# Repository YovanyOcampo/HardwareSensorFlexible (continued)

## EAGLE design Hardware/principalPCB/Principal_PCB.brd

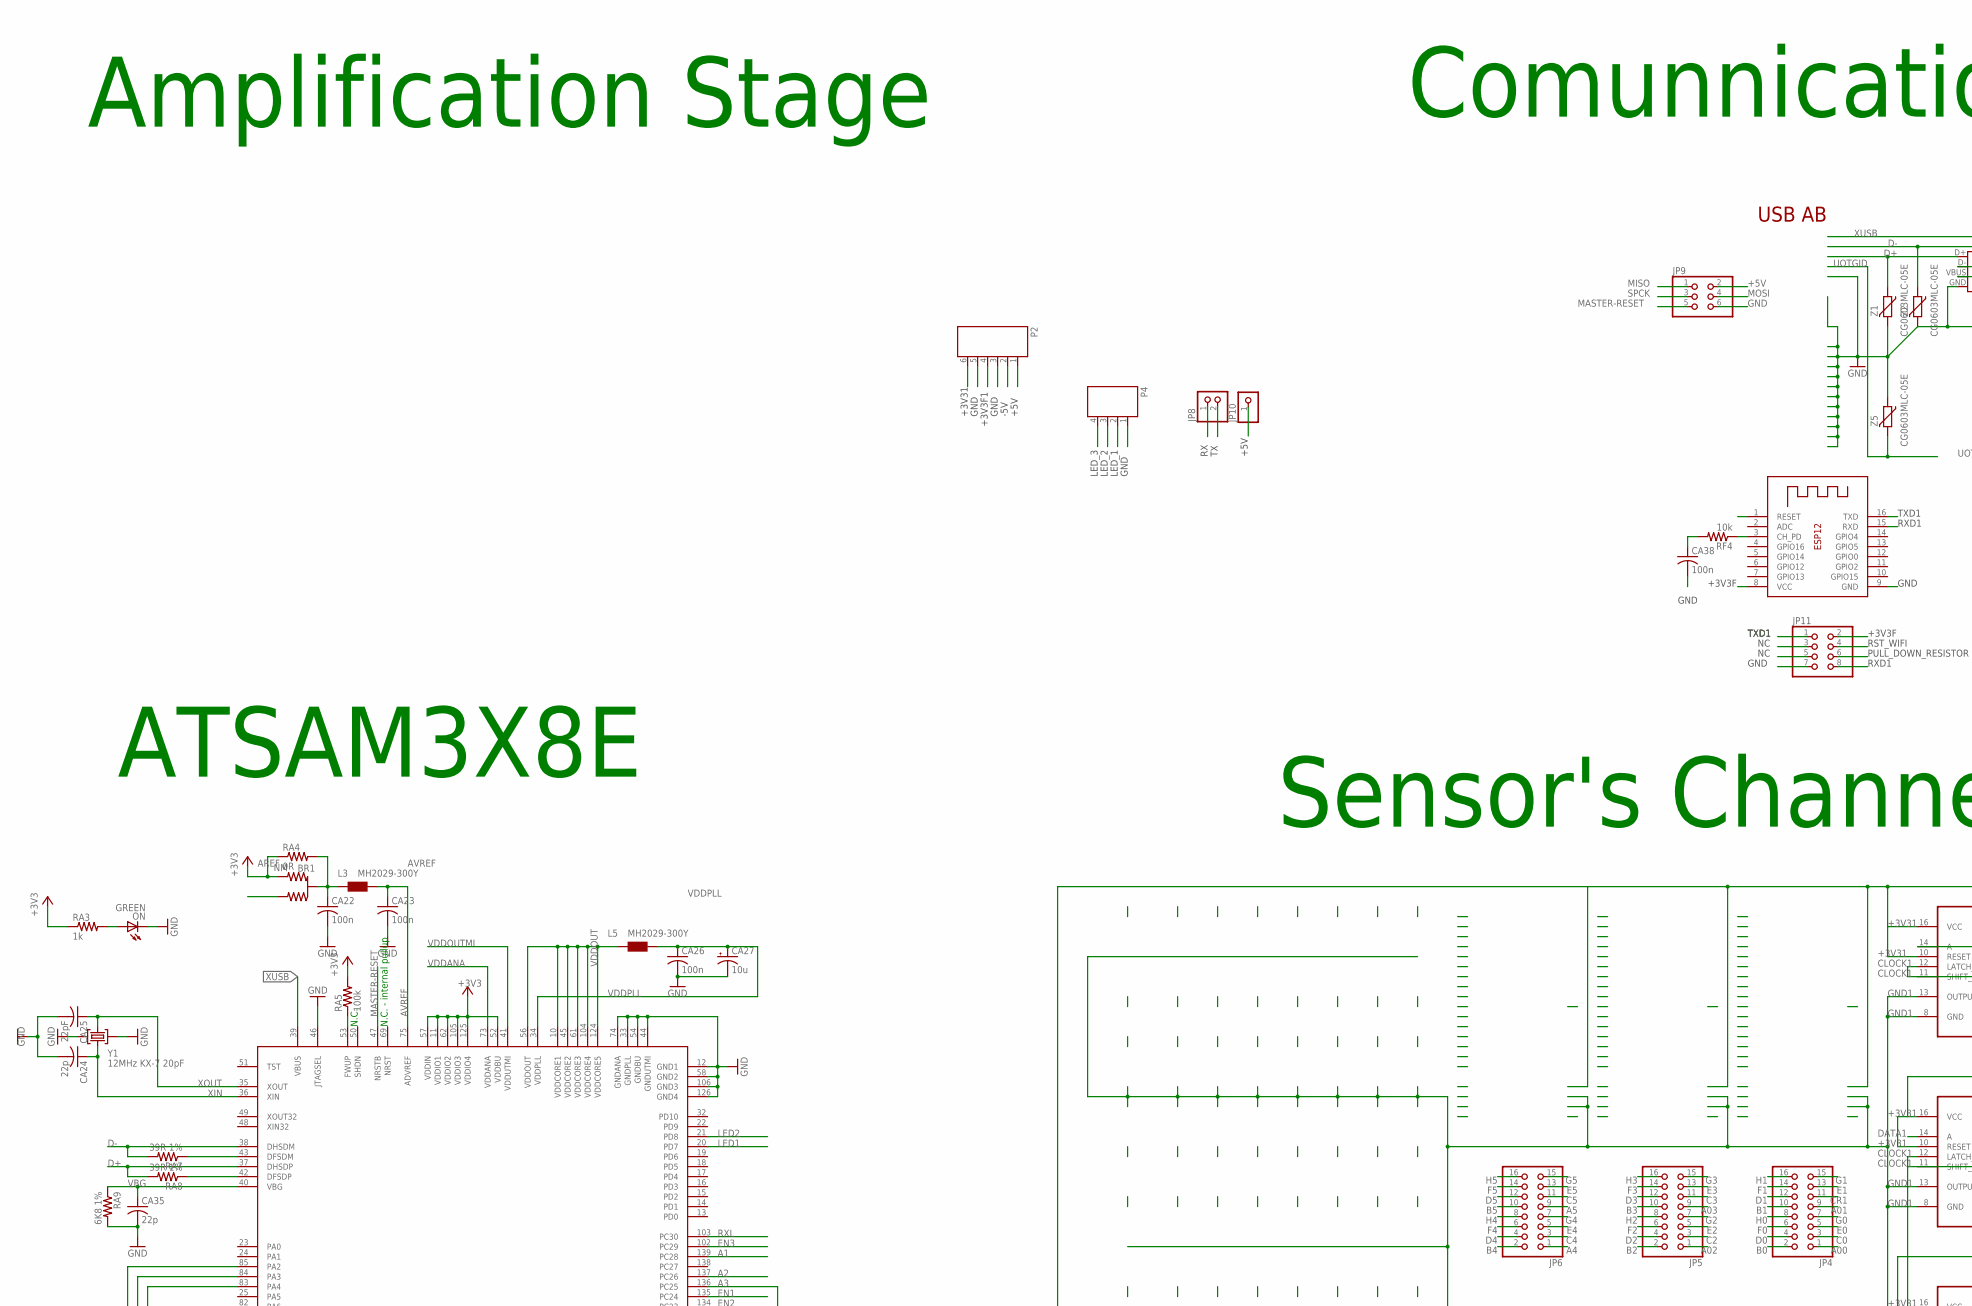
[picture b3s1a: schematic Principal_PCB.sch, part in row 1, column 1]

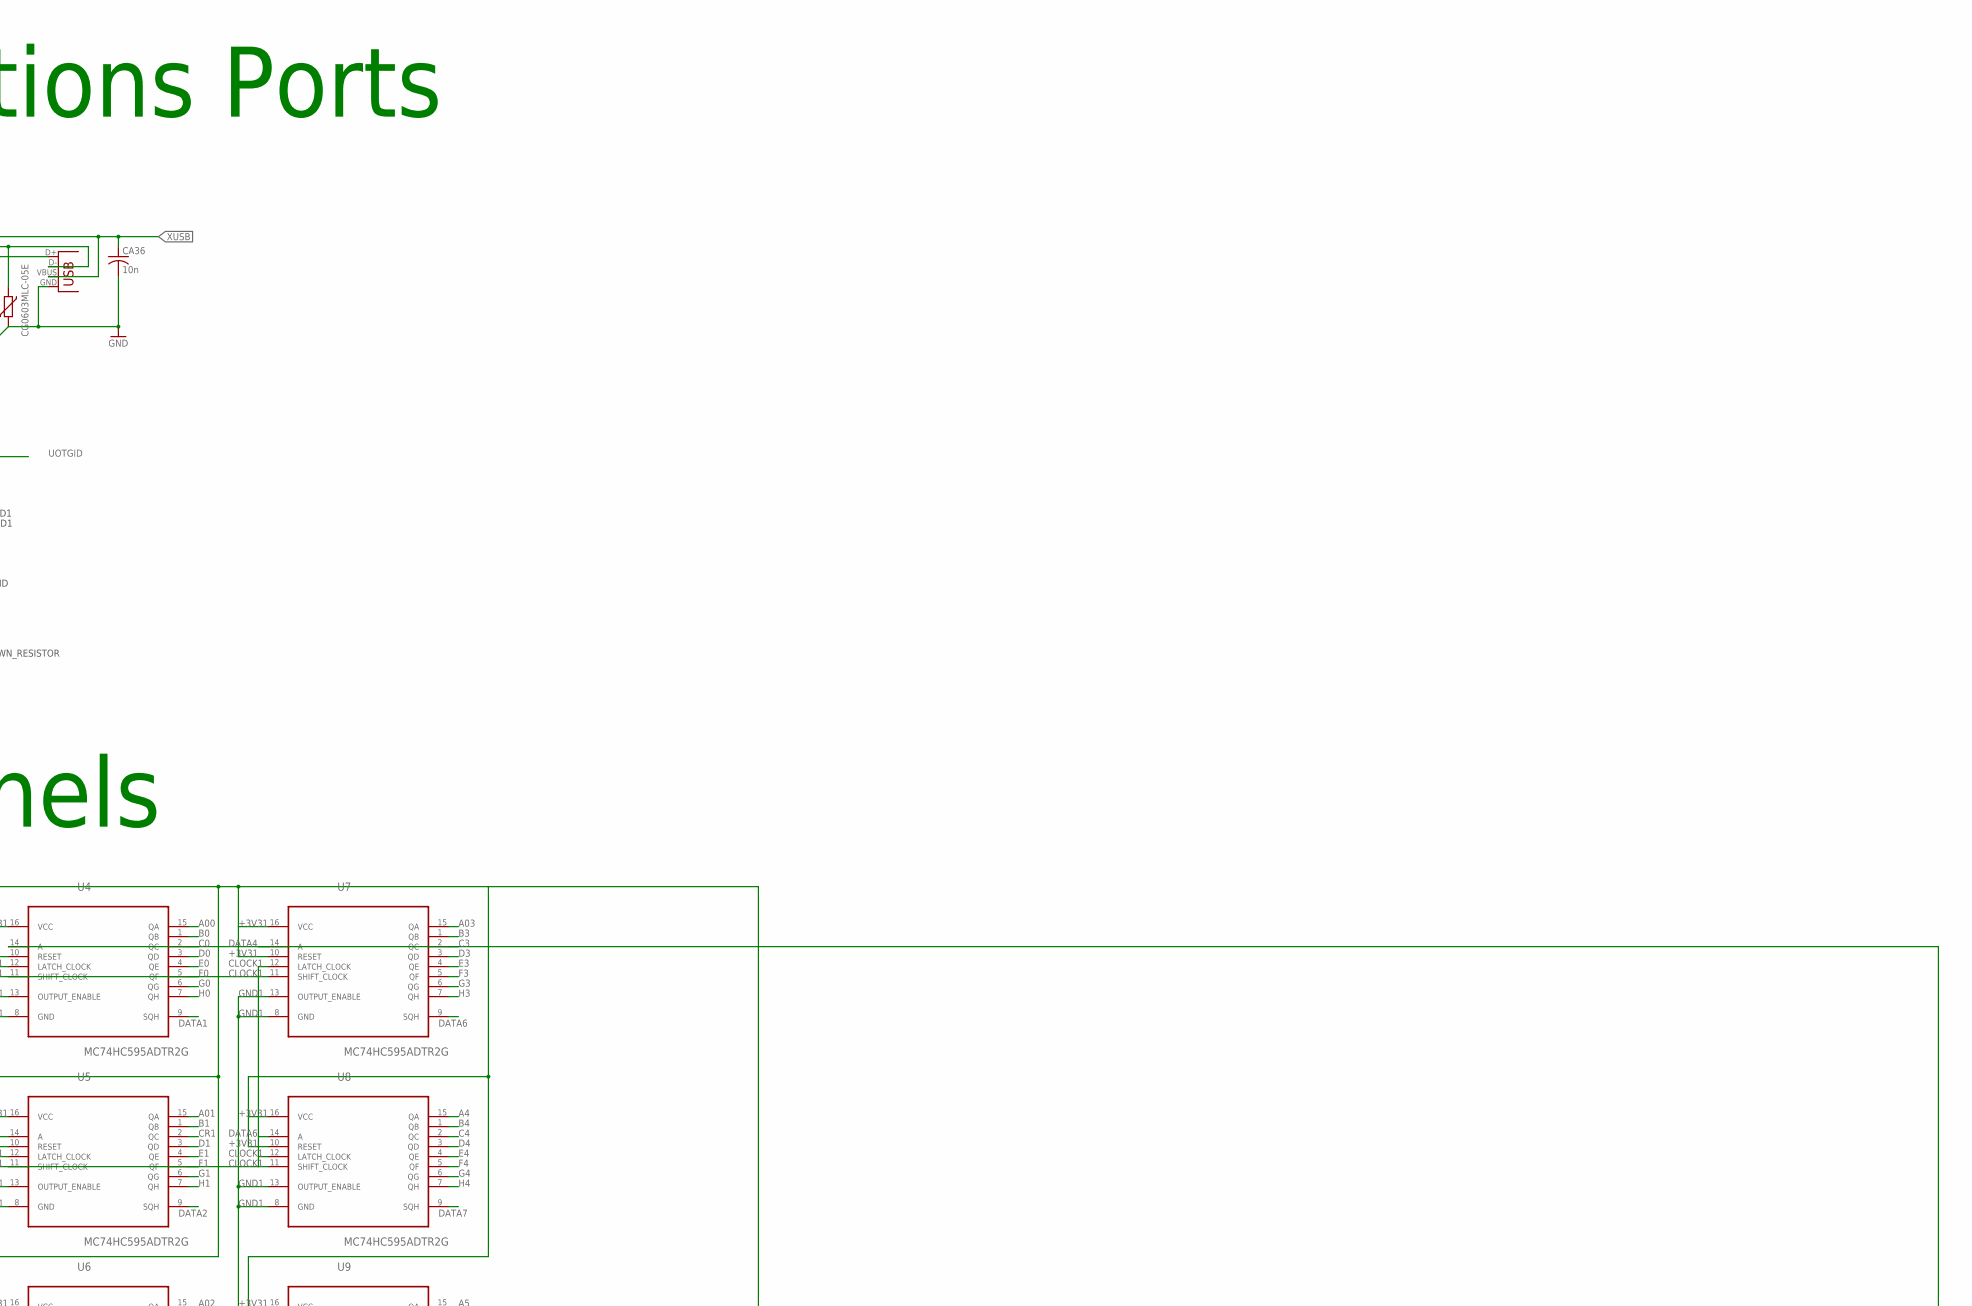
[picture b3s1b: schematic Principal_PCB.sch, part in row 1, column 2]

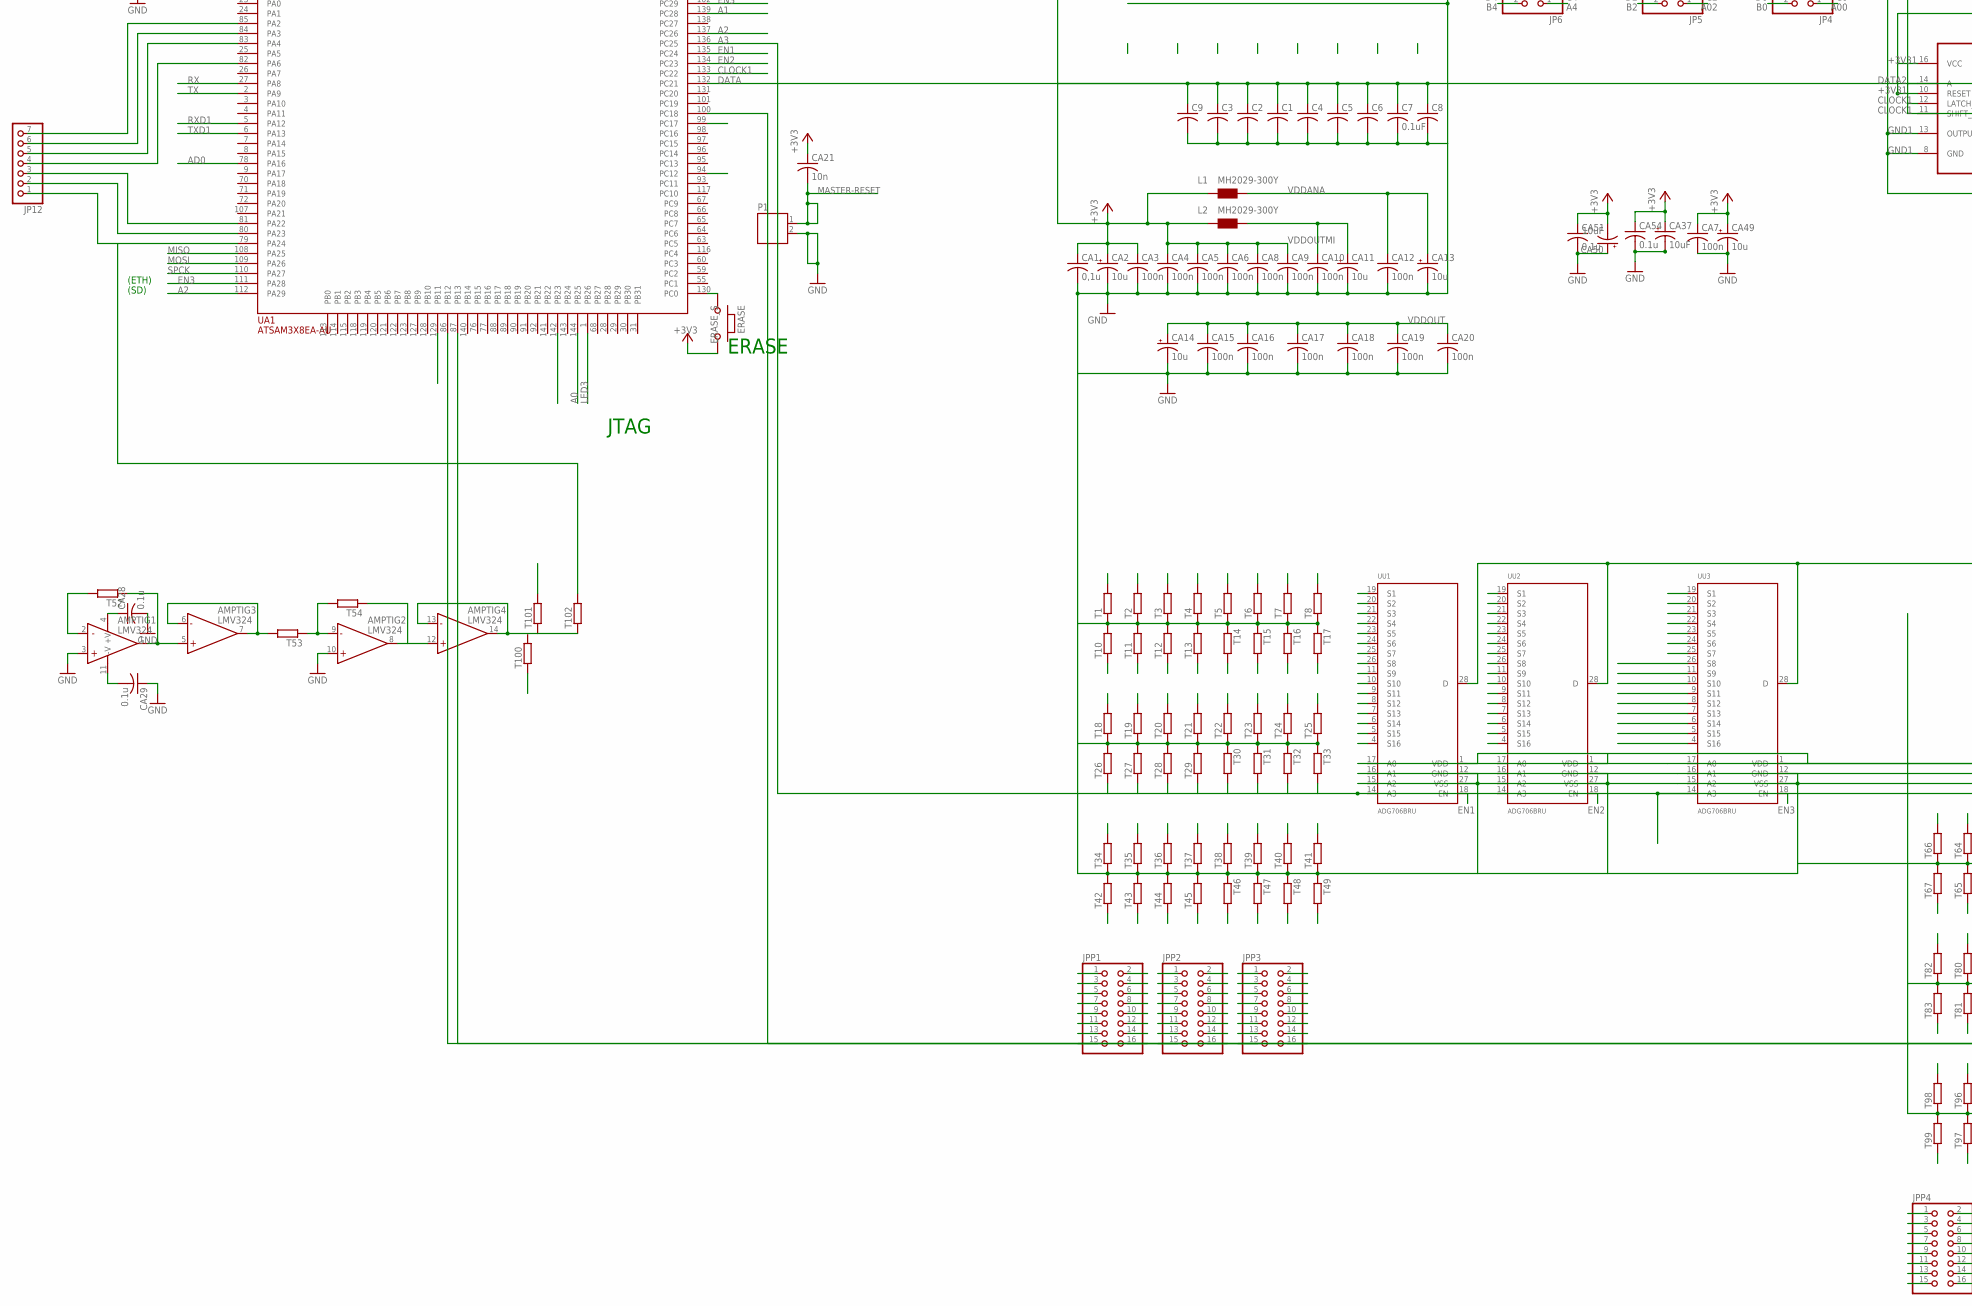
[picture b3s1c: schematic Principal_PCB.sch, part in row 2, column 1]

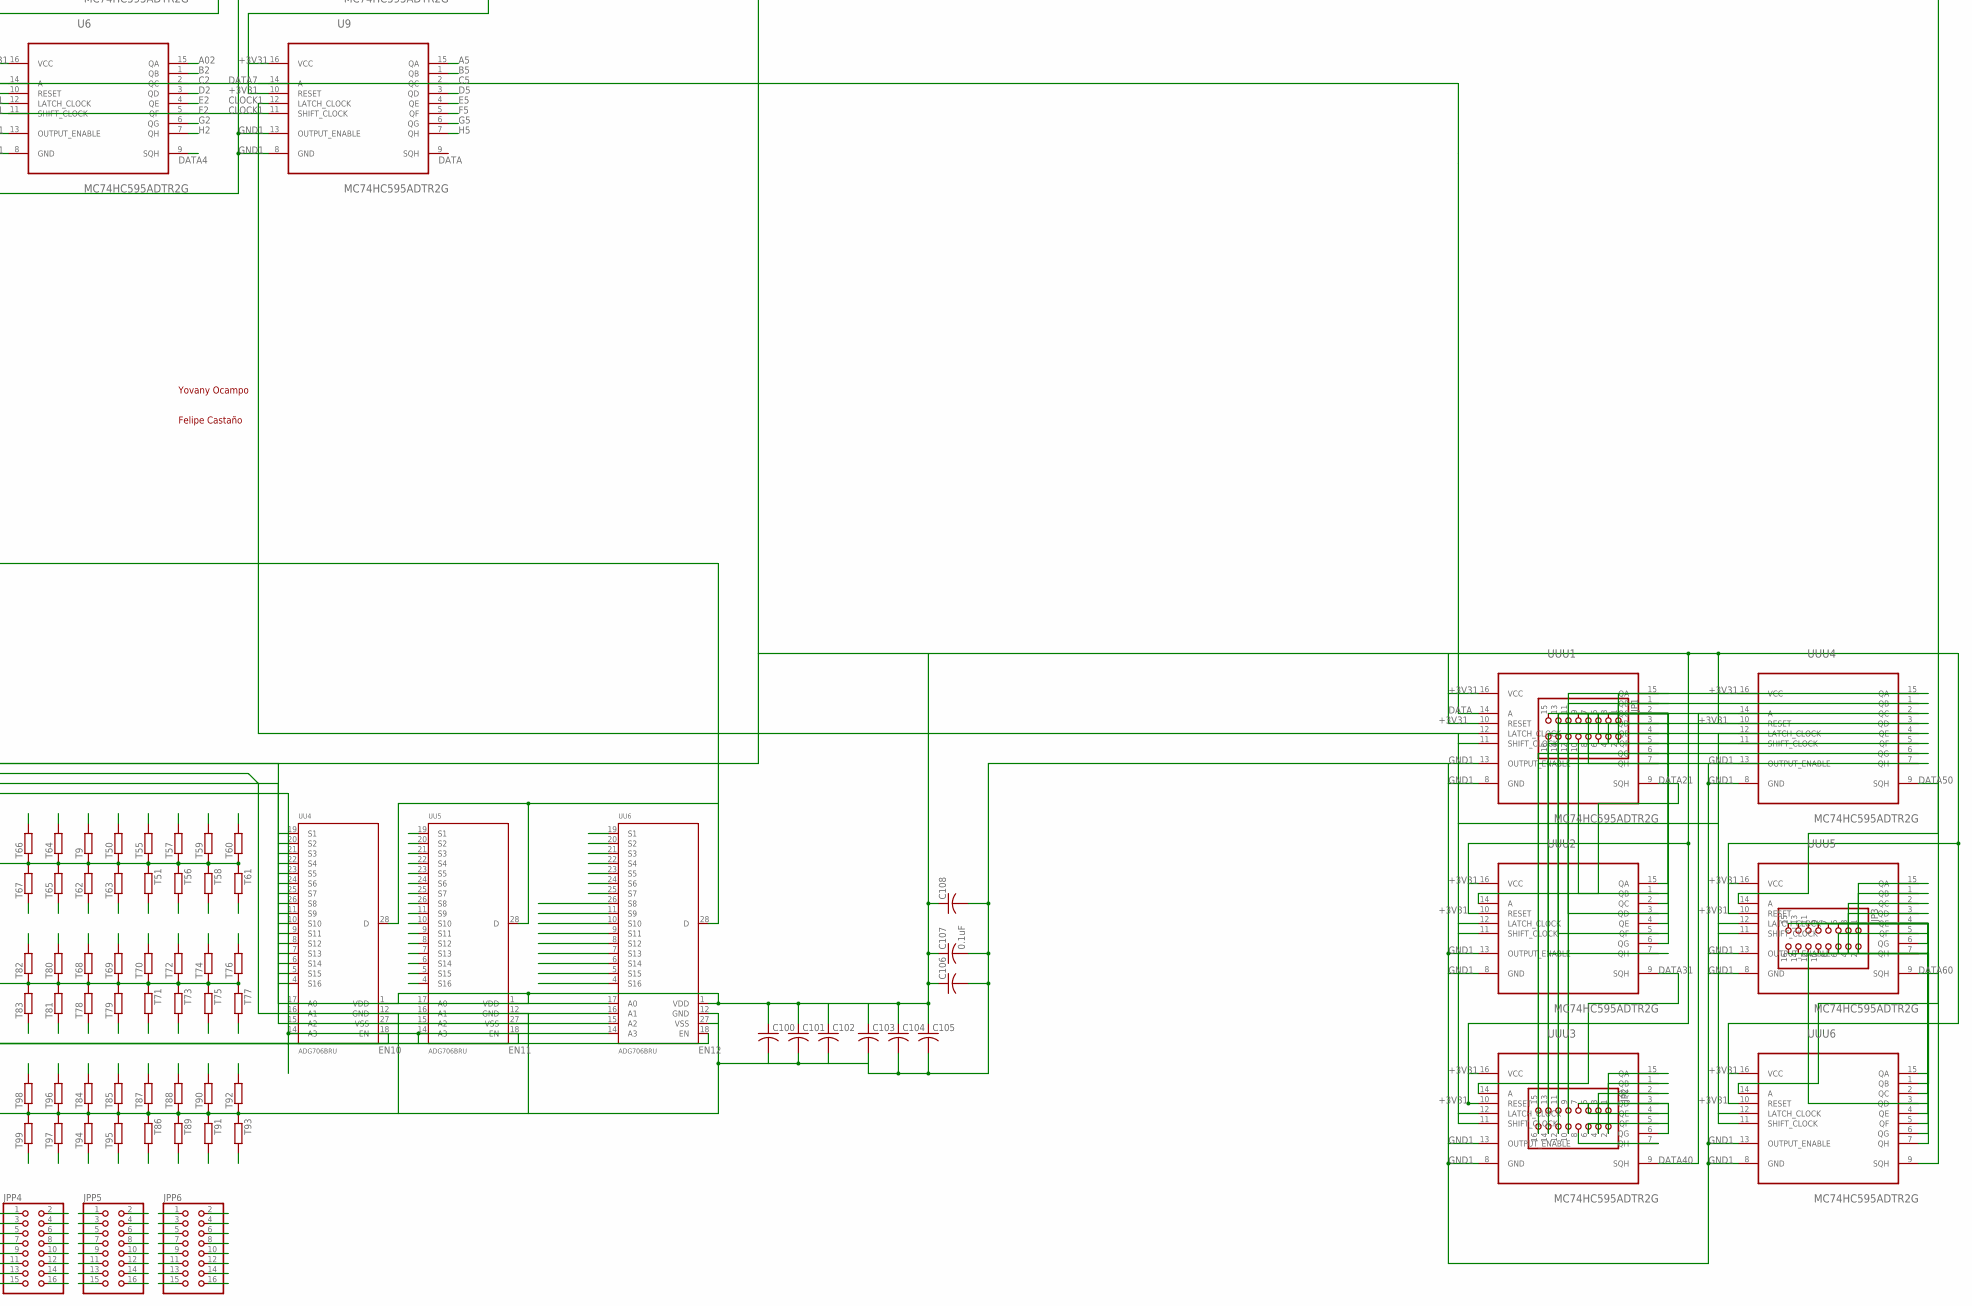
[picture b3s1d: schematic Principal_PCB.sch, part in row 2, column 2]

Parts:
AMPTI: LMV324; SO014
BR1: NM; J0402
C1, C2, C3, C4, C5, C6, C8, C9, C100, C101, C102, C103, C104, C105, C106, C108: C-USC0805; C0805
C7, C107: 0.1uF; C0805
CA1: 0,1u; C0805
CA2, CA11, CA13, CA14, CA27, CA49: 10u; B/3528-21W
CA3, CA4, CA5, CA6, CA7, CA8, CA9, CA10, CA12, CA15, CA16, CA17, CA18, CA19, CA20, CA22, CA23, CA26, CA38: 100n; C0805
CA21, CA36: 10n; C0805
CA24, CA35: 22p; C0805
CA25: 22pF; C0805
CA28, CA29, CA51, CA54: 0.1u; C0805K
CA37, CA50: 10uF; B/3528-21W
ERASE: MYSMD_PB157; SMD_157SW
JP1, JP2, JP3, JP4, JP5, JP6: PINHD-2X8; 2X08
JP8: PINHD-1X2; 1X02
JP9: PINHD-2X3; 2X03
JP10: PINHD-1X1; 1X01
JP11: PINHD-2X4; 2X04
JP12: PINHD-1X7; 1X07
JPP1, JPP2, JPP3, JPP4, JPP5, JPP6: PINHD-2X8; 2X08
L1, L2, L3, L5: MH2029-300Y; 0805
ON: GREEN; CHIP-LED0805
P1: JST-PH2
P2: JST-PH6
P4: JST-PH4
RA3: 1k; R0805
RA4: 0R; R0805
RA5: 100k; R0805
RA7, RA8: 39R 1%; R0805
RA9: 6K8 1%; R0805
RF4: 10k; R0805
T1, T2, T3, T4, T5, T6, T7, T8, T9, T10, T11, T12, T13, T14, T15, T16, T17, T18, T19, T20, T21, T22, T23, T24, T25, T26, T27, T28, T29, T30, T31, T32, T33, T34, T35, T36, T37, T38, T39, T40, T41, T42, T43, T44, T45, T46, T47, T48, T49, T50, T51, T52, T53, T54, T55, T56, T57, T58, T59, T60, T61, T62, T63, T64, T65, T66, T67, T68, T69, T70, T71, T72, T73, T74, T75, T76, T77, T78, T79, T80, T81, T82, T83, T84, T85, T86, T87, T88, T89, T90, T91, T92, T93, T94, T95, T96, T97, T98, T99, T100, T101, T102: R-EU_R0805; R0805
U4, U5, U6, U7, U8, U9: MC74HC595ADTR2G; SOP65P640X120-16N
UA1: ATSAM3X8EA-AU; LQFP144
UU1, UU2, UU3, UU4, UU5, UU6: ADG706BRU; TSSOP28
UUU1, UUU2, UUU3, UUU4, UUU5, UUU6: MC74HC595ADTR2G; SOP65P640X120-16N
X1: ESP-12
X3: USBPTH; USB-B-PTH
Y1: 12MHz KX-7 20pF; CRYSTAL-3.2-2.5
Z1, Z2, Z5: CG0603MLC-05E; CT/CN0603

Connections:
49: JPP4.15, T64.2, UU4.20 (S2)
50: JPP4.16, T66.2, UU4.19 (S1)
51: JPP4.14, T9.2, UU4.21 (S3)
52: JPP4.12, T51.2, UU4.23 (S5)
53: JPP4.11, T55.2, UU4.24 (S6)
54: JPP4.10, T56.2, UU4.25 (S7)
55: JPP4.9, T57.2, UU4.26 (S8)
56: JPP4.7, T59.2, UU4.10 (S10)
57: JPP4.8, T58.2, UU4.11 (S9)
58: JPP4.5, T61.2, UU4.8 (S12)
59: JPP4.6, T60.2, UU4.9 (S11)
60: JPP4.3, T65.1, UU4.6 (S14)
61: JPP4.4, T67.1, UU4.7 (S13)
62: JPP4.1, T63.1, UU4.4 (S16)
63: JPP4.2, T62.1, UU4.5 (S15)
64: JPP4.13, T50.2, UU4.22 (S4)
65: JPP5.15, T80.2, UU5.20 (S2)
66: JPP5.16, T82.2, UU5.19 (S1)
67: JPP5.14, T68.2, UU5.21 (S3)
68: JPP5.12, T70.2, UU5.23 (S5)
69: JPP5.11, T71.2, UU5.24 (S6)
70: JPP5.10, T72.2, UU5.25 (S7)
71: JPP5.9, T73.2, UU5.26 (S8)
72: JPP5.7, T75.2, UU5.10 (S10)
73: JPP5.8, T74.2, UU5.11 (S9)
74: JPP5.5, T77.2, UU5.8 (S12)
75: JPP5.6, T76.2, UU5.9 (S11)
76: JPP5.3, T81.1, UU5.6 (S14)
77: JPP5.4, T83.1, UU5.7 (S13)
78: JPP5.1, T79.1, UU5.4 (S16)
79: JPP5.2, T78.1, UU5.5 (S15)
80: JPP5.13, T69.2, UU5.22 (S4)
81: JPP6.15, T96.2, UU6.20 (S2)
82: JPP6.16, T98.2, UU6.19 (S1)
83: JPP6.14, T84.2, UU6.21 (S3)
84: JPP6.12, T86.2, UU6.23 (S5)
85: JPP6.11, T87.2, UU6.24 (S6)
86: JPP6.10, T88.2, UU6.25 (S7)
87: JPP6.9, T89.2, UU6.26 (S8)
88: JPP6.7, T91.2, UU6.10 (S10)
89: JPP6.8, T90.2, UU6.11 (S9)
90: JPP6.5, T93.2, UU6.8 (S12)
91: JPP6.6, T92.2, UU6.9 (S11)
92: JPP6.3, T97.1, UU6.6 (S14)
93: JPP6.4, T99.1, UU6.7 (S13)
94: JPP6.1, T95.1, UU6.4 (S16)
95: JPP6.2, T94.1, UU6.5 (S15)
96: JPP6.13, T85.2, UU6.22 (S4)
100: JPP1.16, T1.2, UU1.19 (S1)
101: JPP1.15, T2.2, UU1.20 (S2)
102: JPP1.14, T3.2, UU1.21 (S3)
103: JPP1.13, T4.2, UU1.22 (S4)
104: JPP1.11, T5.2, UU1.24 (S6)
105: JPP1.9, T6.2, UU1.26 (S8)
106: JPP1.7, T7.2, UU1.10 (S10)
107: JPP1.6, T8.2, UU1.9 (S11)
108: JPP1.4, T10.1, UU1.7 (S13)
109: JPP1.3, T11.1, UU1.6 (S14)
110: JPP1.2, T12.1, UU1.5 (S15)
111: JPP1.1, T13.1, UU1.4 (S16)
112: JPP1.12, T14.2, UU1.23 (S5)
113: JPP1.10, T15.2, UU1.25 (S7)
114: JPP1.8, T16.2, UU1.11 (S9)
115: JPP1.5, T17.2, UU1.8 (S12)
116: JPP2.16, T18.2, UU2.19 (S1)
117: JPP2.15, T19.2, UU2.20 (S2)
118: JPP2.14, T20.2, UU2.21 (S3)
119: JPP2.13, T21.2, UU2.22 (S4)
120: JPP2.12, T22.2, UU2.23 (S5)
121: JPP2.10, T23.2, UU2.25 (S7)
122: JPP2.8, T24.2, UU2.11 (S9)
123: JPP2.6, T25.2, UU2.9 (S11)
124: JPP2.4, T26.1, UU2.7 (S13)
125: JPP2.3, T27.1, UU2.6 (S14)
126: JPP2.2, T28.1, UU2.5 (S15)
127: JPP2.1, T29.1, UU2.4 (S16)
128: JPP2.11, T30.2, UU2.24 (S6)
129: JPP2.9, T31.2, UU2.26 (S8)
130: JPP2.7, T32.2, UU2.10 (S10)
131: JPP2.5, T33.2, UU2.8 (S12)
132: JPP3.16, T34.2, UU3.19 (S1)
133: JPP3.15, T35.2, UU3.20 (S2)
134: JPP3.14, T36.2, UU3.21 (S3)
135: JPP3.13, T37.2, UU3.22 (S4)
136: JPP3.11, T38.2, UU3.24 (S6)
137: JPP3.10, T39.2, UU3.25 (S7)
138: JPP3.8, T40.2, UU3.11 (S9)
139: JPP3.6, T41.2, UU3.9 (S11)
140: JPP3.4, T42.1, UU3.7 (S13)
141: JPP3.3, T43.1, UU3.6 (S14)
142: JPP3.2, T44.1, UU3.5 (S15)
143: JPP3.1, T45.1, UU3.4 (S16)
144: JPP3.12, T46.2, UU3.23 (S5)
145: JPP3.9, T47.2, UU3.26 (S8)
146: JPP3.7, T48.2, UU3.10 (S10)
147: JPP3.5, T49.2, UU3.8 (S12)
+3V3F1: CA7.1, CA38.1, CA49.+, JP11.2, P2.4, RF4.2, X1.8 (VCC)
+3V31: AMPTI.4 (+V), BR1.3 (2), C1.1, C2.1, C3.1, C4.1, C5.1, C6.1, C7.1, C8.1, C9.1, C100.1, C101.1, C102.1, C103.1, C104.1, C105.1, C106.1, C107.1, C108.1, CA1.1, CA2.+, CA3.1, CA4.1, CA5.1, CA6.1, CA8.1, CA9.1, CA21.1, CA28.1, ERASE.1, JP9.2, L1.1, L2.1, P2.6, RA3.1, RA4.1, RA5.2, U4.10 (RESET), U4.16 (VCC), U5.10 (RESET), U5.16 (VCC), U6.10 (RESET), U6.16 (VCC), U7.10 (RESET), U7.16 (VCC), U8.10 (RESET), U8.16 (VCC), U9.10 (RESET), U9.16 (VCC), UA1.11 (VDDIO1), UA1.52 (VDDBU), UA1.57 (VDDIN), UA1.62 (VDDIO2), UA1.105 (VDDIO3), UA1.125 (VDDIO4), UU1.1 (VDD), UU2.1 (VDD), UU3.1 (VDD), UU4.1 (VDD), UU5.1 (VDD), UU6.1 (VDD), UUU1.10 (RESET), UUU1.16 (VCC), UUU2.10 (RESET), UUU2.16 (VCC), UUU3.10 (RESET), UUU3.16 (VCC), UUU4.10 (RESET), UUU4.16 (VCC), UUU5.10 (RESET), UUU5.16 (VCC), UUU6.10 (RESET), UUU6.16 (VCC)
+5V: CA37.+, CA54.1, JP10.1, P2.1
-5V: AMPTI.11 (-V), CA29.2, CA50.-, CA51.1, P2.2
A0: UA1.144 (PB25), UU1.17 (A0), UU2.17 (A0), UU3.17 (A0), UU4.17 (A0), UU5.17 (A0), UU6.17 (A0)
A00: JP4.1, U4.15 (QA)
A1: UA1.139 (PC28), UU1.16 (A1), UU2.16 (A1), UU3.16 (A1), UU4.16 (A1), UU5.16 (A1), UU6.16 (A1)
A01: JP4.9, U5.15 (QA)
A2: UA1.112 (PA29), UA1.137 (PC26), UU1.15 (A2), UU2.15 (A2), UU3.15 (A2), UU4.15 (A2), UU5.15 (A2), UU6.15 (A2)
A02: JP5.1, U6.15 (QA)
A03: JP5.9, U7.15 (QA)
A3: UA1.136 (PC25), UU1.14 (A3), UU2.14 (A3), UU3.14 (A3), UU4.14 (A3), UU5.14 (A3), UU6.14 (A3)
A4: JP6.1, U8.15 (QA)
A5: JP6.9, U9.15 (QA)
AD0: UA1.78 (PA16)
AREF: BR1.1
AVREF: CA23.1, L3.2, UA1.75 (ADVREF)
AVREFL: BR1.2 (C), CA22.1, L3.1, RA4.2
B0: JP4.2, U4.1 (QB)
B1: JP4.10, U5.1 (QB)
B2: JP5.2, U6.1 (QB)
B3: JP5.10, U7.1 (QB)
B4: JP6.2, U8.1 (QB)
B5: JP6.10, U9.1 (QB)
C0: JP4.3, U4.2 (QC)
C2: JP5.3, U6.2 (QC)
C3: JP5.11, U7.2 (QC)
C4: JP6.3, U8.2 (QC)
C5: JP6.11, U9.2 (QC)
CLOCK1: U4.11 (SHIFT_CLOCK), U4.12 (LATCH_CLOCK), U5.11 (SHIFT_CLOCK), U5.12 (LATCH_CLOCK), U6.11 (SHIFT_CLOCK), U6.12 (LATCH_CLOCK), U7.11 (SHIFT_CLOCK), U7.12 (LATCH_CLOCK), U8.11 (SHIFT_CLOCK), U8.12 (LATCH_CLOCK), U9.11 (SHIFT_CLOCK), U9.12 (LATCH_CLOCK), UA1.133 (PC22), UUU1.11 (SHIFT_CLOCK), UUU1.12 (LATCH_CLOCK), UUU2.11 (SHIFT_CLOCK), UUU2.12 (LATCH_CLOCK), UUU3.11 (SHIFT_CLOCK), UUU3.12 (LATCH_CLOCK), UUU4.11 (SHIFT_CLOCK), UUU4.12 (LATCH_CLOCK), UUU5.11 (SHIFT_CLOCK), UUU5.12 (LATCH_CLOCK), UUU6.11 (SHIFT_CLOCK), UUU6.12 (LATCH_CLOCK)
CR1: JP4.11, U5.2 (QC)
D0: JP4.4, U4.3 (QD)
D1: JP4.12, U5.3 (QD)
D2: JP5.4, U6.3 (QD)
D3: JP5.12, U7.3 (QD)
D4: JP6.4, U8.3 (QD)
D5: JP6.12, U9.3 (QD)
D+: RA8.2, UA1.37 (DHSDP), X3.D+, Z1.1
D-: RA7.2, UA1.38 (DHSDM), X3.D-, Z2.1
DATA: UA1.132 (PC21), UUU1.14 (A)
DATA1: U4.9 (SQH), U5.14 (A)
DATA2: U5.9 (SQH), U6.14 (A)
DATA4: U6.9 (SQH), U7.14 (A)
DATA6: U7.9 (SQH), U8.14 (A)
DATA7: U8.9 (SQH), U9.14 (A)
DATA13: U4.14 (A), UUU6.9 (SQH)
DATA21: UUU1.9 (SQH), UUU2.14 (A)
DATA31: UUU2.9 (SQH), UUU3.14 (A)
DATA40: UUU3.9 (SQH), UUU4.14 (A)
DATA50: UUU4.9 (SQH), UUU5.14 (A)
DATA60: UUU5.9 (SQH), UUU6.14 (A)
E0: JP4.5, U4.4 (QE)
E1: JP4.13, U5.4 (QE)
E2: JP5.5, U6.4 (QE)
E3: JP5.13, U7.4 (QE)
E4: JP6.5, U8.4 (QE)
E5: JP6.13, U9.4 (QE)
EN1: UA1.135 (PC24), UU1.18 (EN)
EN2: UA1.134 (PC23), UU2.18 (EN)
EN3: UA1.102 (PC29), UA1.111 (PA28), UU3.18 (EN)
EN10: UA1.100 (PC18), UU4.18 (EN)
EN11: UA1.87 (PB13), UU5.18 (EN)
EN12: UA1.86 (PB12), UU6.18 (EN)
ERASE_S: ERASE.2, UA1.130 (PC0)
F0: JP4.6, U4.5 (QF)
F1: JP4.14, U5.5 (QF)
F2: JP5.6, U6.5 (QF)
F3: JP5.14, U7.5 (QF)
F4: JP6.6, U8.5 (QF)
F5: JP6.14, U9.5 (QF)
G0: JP4.7, U4.6 (QG)
G1: JP4.15, U5.6 (QG)
G2: JP5.7, U6.6 (QG)
G3: JP5.15, U7.6 (QG)
G4: JP6.7, U8.6 (QG)
G5: JP6.15, U9.6 (QG)
GND: CA28.2, CA29.1
GND1: AMPTI.3 (+IN), AMPTI.10 (+IN), C1.2, C2.2, C3.2, C4.2, C5.2, C6.2, C7.2, C8.2, C9.2, C100.2, C101.2, C102.2, C103.2, C104.2, C105.2, C106.2, C107.2, C108.2, CA1.2, CA2.-, CA3.2, CA4.2, CA5.2, CA6.2, CA7.2, CA8.2, CA9.2, CA10.2, CA11.-, CA12.2, CA13.-, CA14.-, CA15.2, CA16.2, CA17.2, CA18.2, CA19.2, CA20.2, CA22.2, CA23.2, CA24.2, CA25.2, CA26.2, CA27.-, CA35.2, CA36.2, CA37.-, CA38.2, CA49.-, CA50.+, CA51.2, CA54.2, JP9.6, JP11.7, ON.C, P1.2, P2.3, P2.5, P4.1, RA9.2, T1.1, T2.1, T3.1, T4.1, T5.1, T6.1, T7.1, T8.1, T9.1, T10.2, T11.2, T12.2, T13.2, T14.1, T15.1, T16.1, T17.1, T18.1, T19.1, T20.1, T21.1, T22.1, T23.1, T24.1, T25.1, T26.2, T27.2, T28.2, T29.2, T30.1, T31.1, T32.1, T33.1, T34.1, T35.1, T36.1, T37.1, T38.1, T39.1, T40.1, T41.1, T42.2, T43.2, T44.2, T45.2, T46.1, T47.1, T48.1, T49.1, T50.1, T51.1, T55.1, T56.1, T57.1, T58.1, T59.1, T60.1, T61.1, T62.2, T63.2, T64.1, T65.2, T66.1, T67.2, T68.1, T69.1, T70.1, T71.1, T72.1, T73.1, T74.1, T75.1, T76.1, T77.1, T78.2, T79.2, T80.1, T81.2, T82.1, T83.2, T84.1, T85.1, T86.1, T87.1, T88.1, T89.1, T90.1, T91.1, T92.1, T93.1, T94.2, T95.2, T96.1, T97.2, T98.1, T99.2, T100.1, T101.2, U4.8 (GND), U4.13 (OUTPUT_ENABLE), U5.8 (GND), U5.13 (OUTPUT_ENABLE), U6.8 (GND), U6.13 (OUTPUT_ENABLE), U7.8 (GND), U7.13 (OUTPUT_ENABLE), U8.8 (GND), U8.13 (OUTPUT_ENABLE), U9.8 (GND), U9.13 (OUTPUT_ENABLE), UA1.12 (GND1), UA1.33 (GNDPLL), UA1.44 (GNDUTMI), UA1.46 (JTAGSEL), UA1.54 (GNDBU), UA1.58 (GND2), UA1.74 (GNDANA), UA1.106 (GND3), UA1.126 (GND4), UU1.12 (GND), UU1.27 (VSS), UU2.12 (GND), UU2.27 (VSS), UU3.12 (GND), UU3.27 (VSS), UU4.12 (GND), UU4.27 (VSS), UU5.12 (GND), UU5.27 (VSS), UU6.12 (GND), UU6.27 (VSS), UUU1.8 (GND), UUU1.13 (OUTPUT_ENABLE), UUU2.8 (GND), UUU2.13 (OUTPUT_ENABLE), UUU3.8 (GND), UUU3.13 (OUTPUT_ENABLE), UUU4.8 (GND), UUU4.13 (OUTPUT_ENABLE), UUU5.8 (GND), UUU5.13 (OUTPUT_ENABLE), UUU6.8 (GND), UUU6.13 (OUTPUT_ENABLE), X1.9 (GND), X3.GND, Y1.2 (GND), Y1.4 (GND), Z1.2, Z2.2, Z5.1
H0: JP4.8, U4.7 (QH)
H1: JP4.16, U5.7 (QH)
H2: JP5.8, U6.7 (QH)
H3: JP5.16, U7.7 (QH)
H4: JP6.8, U8.7 (QH)
H5: JP6.16, U9.7 (QH)
LED1: P4.2, UA1.20 (PD7)
LED2: P4.3, UA1.21 (PD8)
LED3: P4.4, UA1.1 (PB26)
MASTER-RESET: CA21.2, JP9.5, JP11.4, P1.1, UA1.47 (NRSTB), X1.1 (RESET)
MISO: JP9.1, UA1.108 (PA25)
MOSI: JP9.4, UA1.109 (PA26)
unnamed: JP2.9, UUU4.15 (QA)
unnamed: ON.A, RA3.2
unnamed: JP2.10, UUU4.1 (QB)
unnamed: JP12.2, UA1.80 (PA23)
unnamed: RA5.1, UA1.53 (FWUP)
unnamed: JP12.3, UA1.81 (PA22)
unnamed: JP12.4, UA1.82 (PA6)
unnamed: RA7.1, UA1.43 (DFSDM)
unnamed: RA8.1, UA1.42 (DFSDP)
unnamed: JP12.6, UA1.84 (PA3)
unnamed: JP12.7, UA1.85 (PA2)
unnamed: JP2.11, UUU4.2 (QC)
unnamed: JP2.12, UUU4.3 (QD)
unnamed: JP12.1, T102.2, UA1.79 (PA24)
unnamed: JP2.13, UUU4.4 (QE)
unnamed: JP12.5, UA1.83 (PA4)
unnamed: JP2.14, UUU4.5 (QF)
unnamed: AMPTI.1 (OUT), AMPTI.5 (+IN), T52.1
unnamed: JP2.15, UUU4.6 (QG)
unnamed: AMPTI.6 (-IN), AMPTI.7 (OUT), T53.2
unnamed: AMPTI.9 (-IN), T53.1, T54.2
unnamed: AMPTI.8 (OUT), AMPTI.12 (+IN), T54.1
unnamed: JP2.16, UUU4.7 (QH)
unnamed: JP3.1, UUU5.15 (QA)
unnamed: JP3.2, UUU5.1 (QB)
unnamed: JP3.3, UUU5.2 (QC)
unnamed: JP3.4, UUU5.3 (QD)
unnamed: JP3.5, UUU5.4 (QE)
unnamed: JP3.6, UUU5.5 (QF)
unnamed: JP3.7, UUU5.6 (QG)
unnamed: JP3.8, UUU5.7 (QH)
unnamed: JP1.1, UUU1.15 (QA)
unnamed: JP1.2, UUU1.1 (QB)
unnamed: JP1.3, UUU1.2 (QC)
unnamed: JP1.4, UUU1.3 (QD)
unnamed: JP1.5, UUU1.4 (QE)
unnamed: JP1.6, UUU1.5 (QF)
unnamed: JP1.7, UUU1.6 (QG)
unnamed: JP1.8, UUU1.7 (QH)
unnamed: JP1.9, UUU2.15 (QA)
unnamed: JP1.10, UUU2.1 (QB)
unnamed: JP1.11, UUU2.2 (QC)
unnamed: JP1.12, UUU2.3 (QD)
unnamed: JP1.13, UUU2.4 (QE)
unnamed: JP1.14, UUU2.5 (QF)
unnamed: JP1.15, UUU2.6 (QG)
unnamed: JP1.16, UUU2.7 (QH)
unnamed: JP2.1, UUU3.15 (QA)
unnamed: JP2.2, UUU3.1 (QB)
unnamed: JP2.3, UUU3.2 (QC)
unnamed: JP2.4, UUU3.3 (QD)
unnamed: JP2.5, UUU3.4 (QE)
unnamed: JP2.6, UUU3.5 (QF)
unnamed: JP2.7, UUU3.6 (QG)
unnamed: JP3.9, UUU6.15 (QA)
unnamed: JP3.10, UUU6.1 (QB)
unnamed: JP3.11, UUU6.2 (QC)
unnamed: JP3.12, UUU6.3 (QD)
unnamed: JP3.13, UUU6.4 (QE)
unnamed: JP3.14, UUU6.5 (QF)
unnamed: JP3.15, UUU6.6 (QG)
unnamed: JP3.16, UUU6.7 (QH)
unnamed: JP2.8, UUU3.7 (QH)
NC: JP11.3
PULL_DOWN_RESISTOR: JP11.6, RF4.1, X1.3 (CH_PD)
RX: JP8.1, UA1.27 (PA8)
RXD1: JP11.8, UA1.5 (PA12), X1.16 (TXD)
RXL: UA1.103 (PC30)
SN100: AMPTI.2 (-IN), T52.2, UU1.28 (D), UU2.28 (D), UU3.28 (D), UU4.28 (D), UU5.28 (D), UU6.28 (D)
SN1000: AMPTI.13 (-IN), AMPTI.14 (OUT), T100.2, T101.1, T102.1
SPCK: JP9.3, UA1.110 (PA27)
SS3: UA1.142 (PB23)
TX: JP8.2, UA1.2 (PA9)
TXD1: JP11.1, UA1.6 (PA13), X1.15 (RXD)
UOTGID: UA1.129 (PB11), Z5.2
VBG: CA35.1, RA9.1, UA1.40 (VBG)
VDDANA: CA12.1, CA13.+, L1.2, UA1.73 (VDDANA)
VDDOUT: CA14.+, CA15.1, CA16.1, CA17.1, CA18.1, CA19.1, CA20.1, L5.1, UA1.10 (VDDCORE1), UA1.45 (VDDCORE2), UA1.56 (VDDOUT), UA1.61 (VDDCORE3), UA1.104 (VDDCORE4), UA1.124 (VDDCORE5)
VDDOUTMI: CA10.1, CA11.+, L2.2, UA1.41 (VDDUTMI)
VDDPLL: CA26.1, CA27.+, L5.2, UA1.34 (VDDPLL)
XIN: CA24.1, UA1.36 (XIN), Y1.1 (C1)
XOUT: CA25.1, UA1.35 (XOUT), Y1.3 (C2)
XUSB: CA36.1, UA1.39 (VBUS), X3.VBUS

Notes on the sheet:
USB AB
N.C.
JTAG
ERASE
(ETH)
(SD)
N.C. - internal pullup
LED3
MISO
SPCK
MOSI
MASTER-RESET
+5V
GND
Sensor's Channels
Comunnications Ports
ATSAM3X8E
Amplification Stage
Yovany Ocampo
Felipe Castaño
+3V3F
RST_WIFI
PULL_DOWN_RESISTOR
RXD1
TXD1
LED_3
LED_2
LED_1
+3V31
+3V3F1
-5V

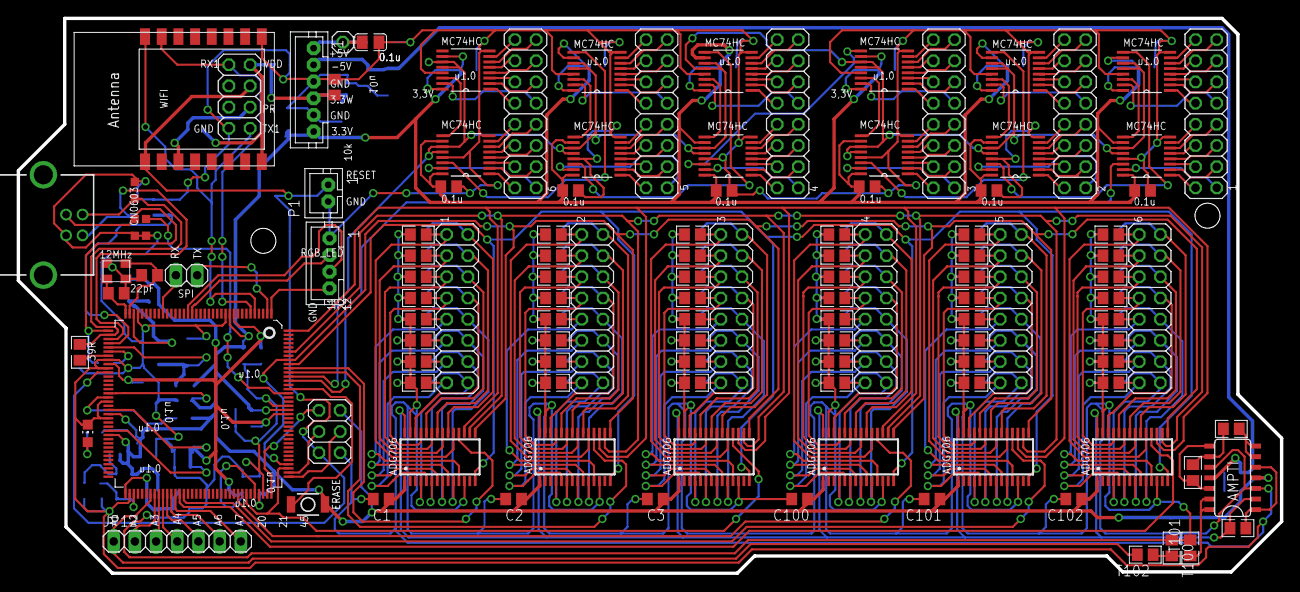
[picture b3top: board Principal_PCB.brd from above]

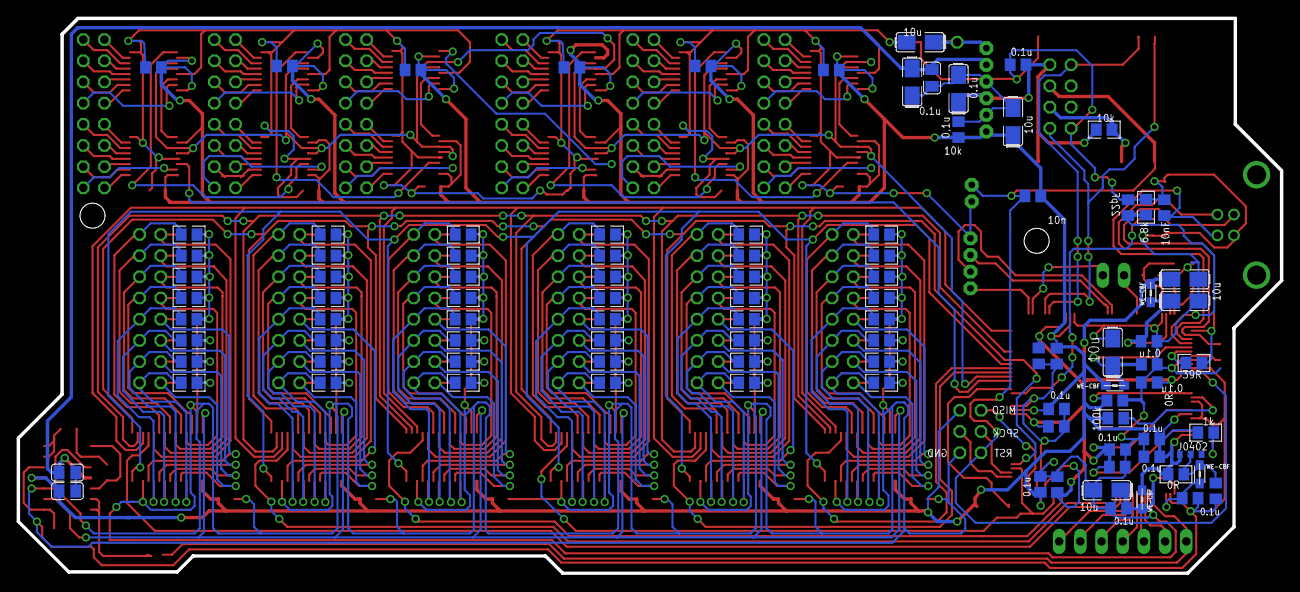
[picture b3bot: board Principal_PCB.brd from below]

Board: 2 copper layers, 151.4 x 66.5 mm, 217 parts (98 on the bottom side), 264 nets.

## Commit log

2018-03-12 Principal PCB and power supply ready
2018-03-12 Amplification stage added and sensing line modified
2018-03-12 PCB for two-stage sensing control and new topology
2018-03-12 PCB principal for two modules and pcb flaxible connector
